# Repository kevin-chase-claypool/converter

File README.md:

# Theta Pen Plotter — System Integration Project

A polar (XY + rotating-bed) pen-plotting system. SVG artwork is converted on a
host PC into G-code for a machine whose **bed rotates under an XY gantry**, with a
force-controlled pen. This repository is split into independent components so each
can be edited and iterated on its own.

## Components

| Folder | What it is | Language / target |
|---|---|---|
| [`software/`](software/) | Host desktop app: SVG → G-code converter with a live Qt/OpenGL preview | Python 3 + PySide6 |
| [`firmware/`](firmware/) | Machine controller (motion via grblHAL) + the pen-pressure control system | grblHAL on RP23CNC; SparkFun Pro Micro RP2350 on the toolhead |
| [`docs/`](docs/) | Design/handoff notes and the System Integration in Robotics report | Markdown |
| [`samples/`](samples/) | Example SVG inputs and generated G-code outputs | assets |

New contributors and AI sessions should begin with
[`docs/START_HERE.md`](docs/START_HERE.md). It links the hardware inventory,
engineering log, master wiring table, architecture, interface contracts,
roadmap, test plan, and the categorized
[`change index`](docs/changes/INDEX.md).

For architecture, dependency, impact, or cross-subsystem investigations using
the local Ontoly graph, begin with the reusable
[`ONTOLY_PROMPT.md`](ONTOLY_PROMPT.md). It pairs graph evidence with the
authoritative interface, wiring, and commissioning records.

For a quick status view, open
[`project_management_overview.html`](project_management_overview.html) from the
repository root. It summarizes the active phase, current blockers, next work,
and links back to the controlling project documents.

## Run the converter

Double-click **`converter.bat`** (launches the Qt/OpenGL app and logs to
`software/qt_debug.log`), or:

```powershell
python software\qt_svg_to_gcode.pyw
```

See [`software/README.md`](software/README.md) for full usage and settings.

## System overview

```
   SVG  ──►  software/ (host)  ──►  .gcode  ──►  ioSender  ──►  RP23CNC + grblHAL  ──►  machine
                                                              │
                                                              └─ M3/M5 tool output ──►  pen-pressure MCU
```

- The host converter maps SVG artwork (bed-local coordinates) into machine
  `X/Y/A` moves for the rotating bed, and emits pen up/down as `M3`/`M5`.
- ioSender is the operator-facing G-code sender: it streams the saved G-code to
  RP23CNC over USB or Ethernet and provides the console, settings, jog, and
  status interface during setup and operation.
- grblHAL on RP23CNC parses the streamed G-code and drives the X/Y/A steppers.
- The pen-pressure system is an independent closed loop that treats the grblHAL
  `M3`/`M5` spindle/tool output state as a **mode override** (engage / lift) and
  otherwise holds a target contact force.

Use [`docs/README.md`](docs/README.md) to find the current architecture,
interfaces, tests, and open work. [`docs/HANDOFF.md`](docs/HANDOFF.md) retains
converter history and technical tradeoffs.

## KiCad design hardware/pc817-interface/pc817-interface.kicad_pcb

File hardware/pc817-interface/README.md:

# PC817C three-channel isolated interface

The current construction source is the minimum-wire, all-through-hole version:

- [`pc817-perfboard-v2-minwire.kicad_pcb`](pc817-perfboard-v2-minwire.kicad_pcb)
- [`pc817-perfboard-v2-minwire.kicad_sch`](pc817-perfboard-v2-minwire.kicad_sch)
- [`pc817-perfboard-v2-minwire.kicad_pro`](pc817-perfboard-v2-minwire.kicad_pro)
- [`PERFBOARD_BUILD.md`](PERFBOARD_BUILD.md)
- [`PRO_MICRO_JST_HARNESS.md`](PRO_MICRO_JST_HARNESS.md)

The board remains 40.16 × 22.65 mm on a 14 × 6, 2.54 mm grid. It uses only
through-hole parts, two 1×6 2.54 mm screw terminals on the short sides, and two
mounting holes on the right short side. It can be fabricated as a two-layer PCB
or followed as a point-to-point perfboard wiring map.

The v2 placement is optimized around complete electrical nets rather than the
appearance of three identical rows. U1 and U2 face the same direction for the
controller-to-toolhead paths. U3 is deliberately rotated 180 degrees because
its signal travels from the toolhead back to the controller. That rotation,
channel-aligned terminal order, and omission of the optional C3 rail bypass
reduce the recovered v1 route from 110 segments / 337.35 mm to 38 segments /
161.83 mm: 65% fewer segments and 52% less routed length. There are no vias.

The direct-header harness uses `GP29` (U1 M3/M5), `GP28` (U2 `HOME_ARM`), and
`GP27` (U3 `A_HOME`) so the PC817 connector can occupy the consecutive Pro
Micro run `GND`, `RST` (NC), `3V3`, `GP29`, `GP28`, `GP27`. U1/U2 outputs are
active-low: R3/R4 pull GP29/GP28 to local 3.3 V while an illuminated PC817
pulls the corresponding input to `TOOL_GND`. Controller and toolhead grounds
remain galvanically isolated.

U3 is the reverse `GP27` to `A_HOME` channel. The RP23CNC `LIMA` input is a 12 V
active-low input that asserts when U3 sinks it to `CTRL_GND`; neither 12 V nor
3.3 V is driven into `A_HOME`. A bench test of the installed U3 sample, using
12 V and a 2.2 kΩ simulated controller load, measured approximately 12 V idle
and 0.2 V asserted. The completed bench assembly passed the same U1/U2/U3
circuit tests on the prior GP8/GP20/GP9 map; repeat them after repinning to
GP29/GP28/GP27. R6 may now be a direct `A_HOME`-to-`A_HOME_SW` wire or a 0 Ω
link.
This sample-specific measurement does not change the generic PC817C CTR limit;
test again if U3 is replaced.

KiCad 10.0.5 verification of v2 reports zero ERC violations, zero error-level
DRC violations, zero unconnected pads, and zero schematic-parity issues. An
independent exported-netlist audit matched all 46 schematic component pins to
their PCB pads, including both six-position terminal blocks. The
full visual DRC may still flag dense silkscreen clearances; those warnings do
not represent electrical faults and should be reviewed if manufacturing a PCB.

The v1.2 files and older rendered diagrams are retained as historical evidence.
The manually recovered `pc817-perfboard-v1.2-routed.kicad_pcb` contains known
shorts/opens and must not be used as a construction source.

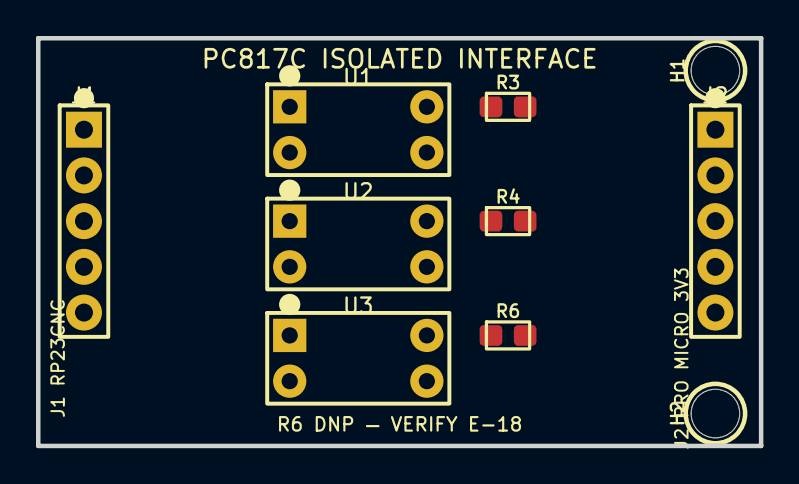
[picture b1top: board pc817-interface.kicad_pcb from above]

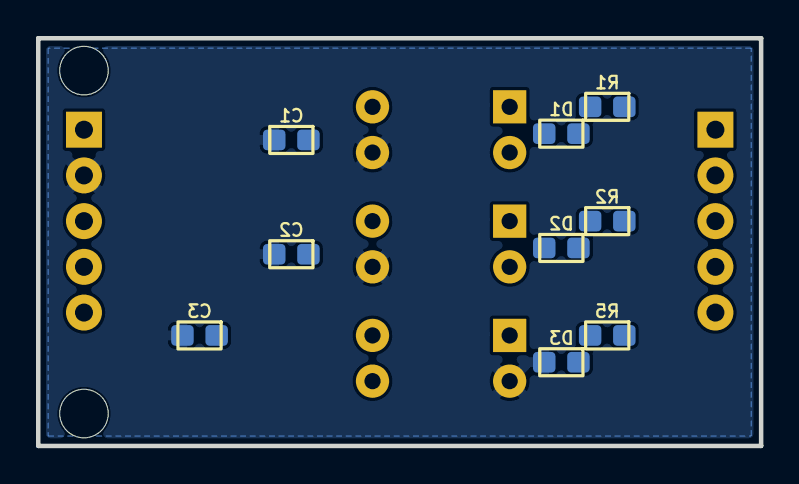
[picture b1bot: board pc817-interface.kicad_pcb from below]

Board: 2 copper layers, 40.2 x 22.6 mm, 19 parts (9 on the bottom side), 14 nets, no tracks yet.

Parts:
C1, C2: 47nF; 47nF_0805
C3: 100nF; 100nF_0805
D1, D2, D3: 1N4148W; 1N4148W_0805
H1, H2: MountingHole_2.5mm
J1: RP23CNC 2.54mm RA; RA_Header_1x05_2.54mm
J2: PRO MICRO 2.54mm RA; RA_Header_1x05_2.54mm
R1, R2: 680R; 680R_0805
R3, R4: 10k; 10k_0805
R5: 390R; 390R_0805
R6: 0R_DNP; 0R_DNP_0805
U1, U2, U3: PC817C; PC817_DIP4

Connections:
AUX0: D2.2, J1.4, U2.2
A_HOME: J1.5, R6.2
A_HOME_SW: R6.1, U3.4
CTRL_5V: J1.1, R1.1, R2.1
CTRL_GND: J1.2, U3.3
ENA: D1.2, J1.3, U1.2
GP8: C1.1, J2.3, R3.1, U1.4
GP9: J2.5, R5.1
GP10: C2.1, J2.4, R4.1, U2.4
LED1_A: D1.1, R1.2, U1.1
LED2_A: D2.1, R2.2, U2.1
LED3_A: D3.1, R5.2, U3.1
TOOL_3V3: C3.1, J2.1, R3.2, R4.2
TOOL_GND: C1.2, C2.2, C3.2, D3.2, J2.2, U1.3, U2.3, U3.2

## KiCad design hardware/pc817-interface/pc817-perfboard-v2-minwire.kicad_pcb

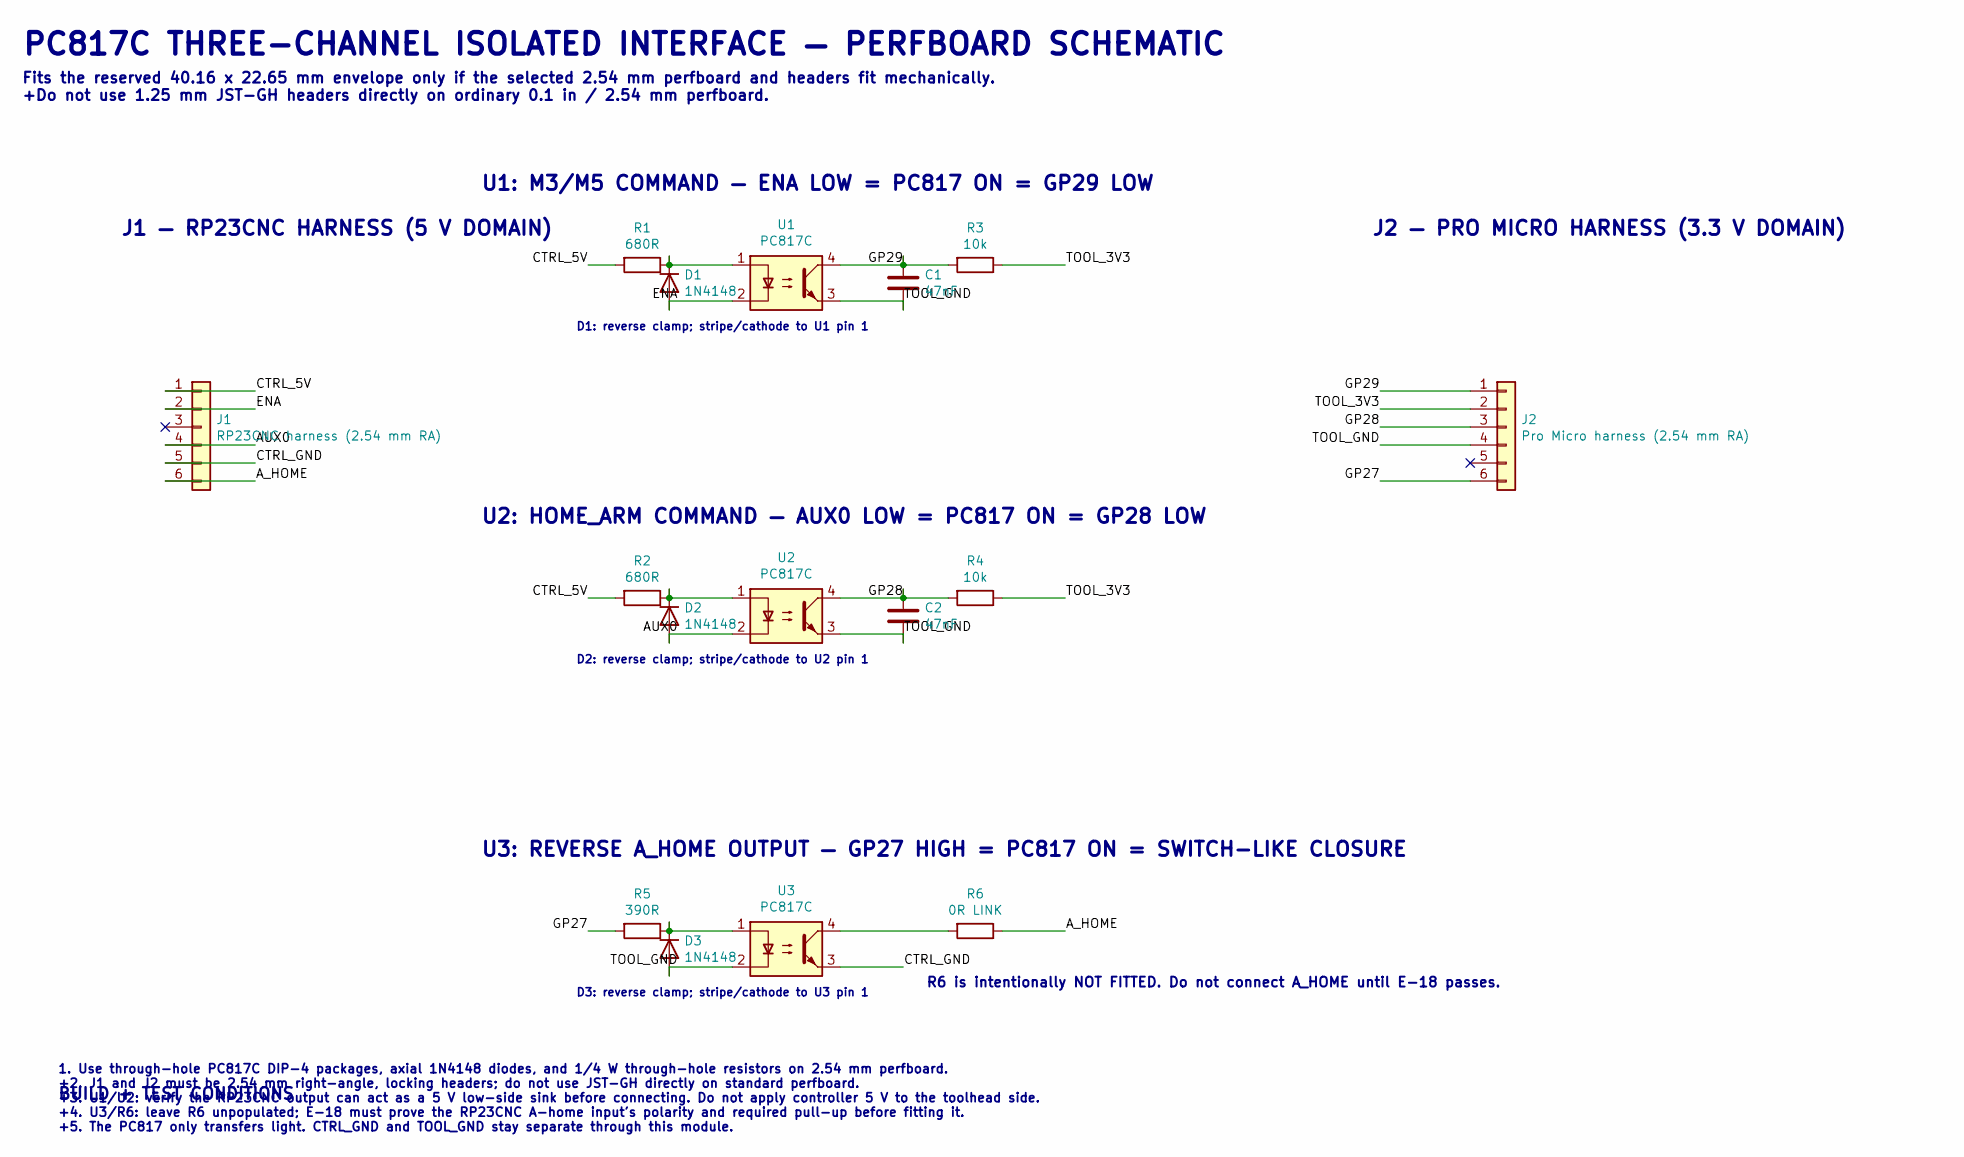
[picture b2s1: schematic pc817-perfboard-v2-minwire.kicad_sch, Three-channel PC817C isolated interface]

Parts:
C1, C2: 47nF
D1, D2, D3: 1N4148; D_DO-35_SOD27_P10.16mm_Horizontal
J1: RP23CNC harness (2.54 mm RA)
J2: Pro Micro harness (2.54 mm RA)
R1, R2: 680R
R3, R4: 10k
R5: 390R
R6: 0R LINK
U1, U2, U3: PC817C; DIP-4_W7.62mm

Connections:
AUX0: D2.2 (A), J1.4, U2.2
A_HOME: J1.6, R6.1
A_HOME_SW: R6.2, U3.4
CTRL_5V: J1.1, R1.2, R2.2
CTRL_GND: J1.5, U3.3
ENA: D1.2 (A), J1.2, U1.2
GP27: J2.6, R5.2
GP28: C2.1, J2.3, R4.2, U2.4
GP29: C1.1, J2.1, R3.2, U1.4
LED1_A: D1.1 (K), R1.1, U1.1
LED2_A: D2.1 (K), R2.1, U2.1
LED3_A: D3.1 (K), R5.1, U3.1
TOOL_3V3: J2.2, R3.1, R4.1
TOOL_GND: C1.2, C2.2, D3.2 (A), J2.4, U1.3, U2.3, U3.2

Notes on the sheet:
D2: reverse clamp; stripe/cathode to U2 pin 1
R6 is intentionally NOT FITTED. Do not connect A_HOME until E-18 passes.
U3: REVERSE A_HOME OUTPUT — GP27 HIGH = PC817 ON = SWITCH-LIKE CLOSURE
BUILD + TEST CONDITIONS
1. Use through-hole PC817C DIP-4 packages, axial 1N4148 diodes, and 1/4 W through-hole resistors on 2.54 mm perfboard. +2. J1 and J2 must be 2.54 mm right-angle, locking headers; do not use JST-GH directly on standard perfboard. +3. U1/U2: verify the RP23CNC output can act as a 5 V low-side sink be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
D3: reverse clamp; stripe/cathode to U3 pin 1
D1: reverse clamp; stripe/cathode to U1 pin 1
U2: HOME_ARM COMMAND — AUX0 LOW = PC817 ON = GP28 LOW
PC817C THREE-CHANNEL ISOLATED INTERFACE — PERFBOARD SCHEMATIC
J2 — PRO MICRO HARNESS (3.3 V DOMAIN)
J1 — RP23CNC HARNESS (5 V DOMAIN)
Fits the reserved 40.16 x 22.65 mm envelope only if the selected 2.54 mm perfboard and headers fit mechanically. +Do not use 1.25 mm JST-GH headers directly on ordinary 0.1 in / 2.54 mm perfboard.
U1: M3/M5 COMMAND — ENA LOW = PC817 ON = GP29 LOW

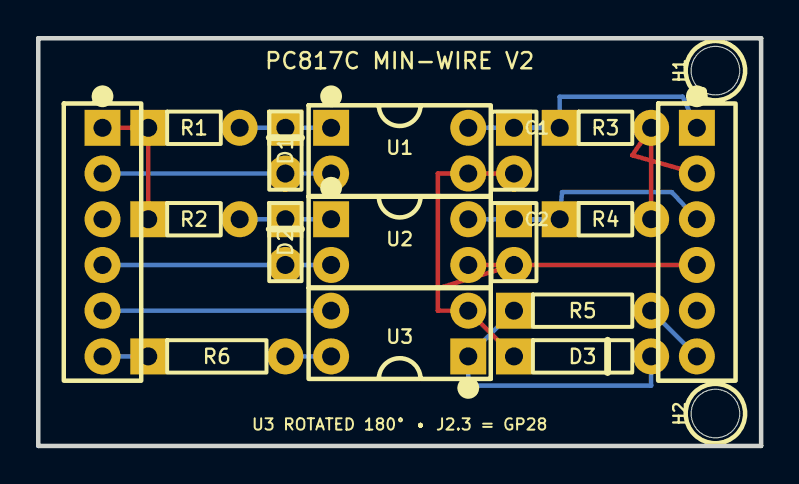
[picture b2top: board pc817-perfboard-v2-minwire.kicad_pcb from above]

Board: 2 copper layers, 40.2 x 22.6 mm, 18 parts (0 on the bottom side), 14 nets.

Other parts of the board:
H1, H2: Perfboard_MountingHole_2.7
